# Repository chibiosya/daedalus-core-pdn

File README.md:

# daedalus-core-pdn

Supplied KiCad 8 board asset for the Daedalus core power-delivery-network (PDN) exercise: a
60 x 40 mm, 4-layer board carrying a 225-ball SoC (U1) with its core-supply fanout, a VRM output
(U2), a GND plane, a VDD_CORE plane, four mounting holes and a set of named keepout areas. It is
meant to be designed *onto*: you add decoupling capacitors, their vias and tracks; everything that
is already here is a **supplied item** and must not be moved or changed.

| File | Purpose |
|---|---|
| `daedalus_core_pdn.kicad_pcb` | The board (KiCad 8 format, version 20240108, all footprints embedded, zones filled) |
| `daedalus_core_pdn.kicad_pro` | Project: numeric design-rule constraints and the `Default` net class |
| `daedalus_core_pdn.kicad_dru` | Custom rules: no via-in-pad, the keepout rules, the mounting-hole copper keepout |
| `supplied_items.json` | UUID + geometry of every supplied item (footprints, tracks, vias, zones, rule areas, edge cuts, groups) and the U1 ball map |
| `tools/` | Reproducible generator / zone filler / verifier / build script |
| `images/` | SVG renders of F.Cu, B.Cu, In1.Cu and In2.Cu |

**Keep the three `daedalus_core_pdn.*` files together.** `kicad-cli pcb drc` loads the `.kicad_pro`
and `.kicad_dru` that sit next to the board; without them KiCad falls back to its defaults
(0.2 mm net-class clearance) and the supplied BGA fanout no longer passes DRC.

## Validation status (KiCad 8.0.9, `kicad-cli`)

```
kicad-cli pcb drc --severity-error   --exit-code-violations daedalus_core_pdn.kicad_pcb   -> exit 0, 0 violations, 0 unconnected
kicad-cli pcb drc --severity-warning --exit-code-violations daedalus_core_pdn.kicad_pcb   -> exit 0, 0 violations (no warnings remain)
```

The keepout rules were proven to fire with a negative-test board (`tools/generate_board.py
--negative-test`): a C_0402 capacitor placed inside KO_BGA_TOP, a via inside KO_VRM, a track inside
KO_DDR_CHANNEL on B.Cu, a via inside KO_MH1 and a via inside a non-U2 SMD pad are each reported as
an error by the corresponding rule (`ko_bga_top`, `ko_vrm`, `ko_ddr_channel`, `ko_mh1` +
`mounting_hole_copper_keepout`, `no_via_in_pad`), and a via centred between two adjacent U1 balls
(A1/A2, at 94.8, 74.4) fails on `clearance` to the ball pads while `ko_bga_top` fires only on the
capacitor, not on any via. A positive-test board (`--positive-test`) with one via at an outer-ring
interstitial position of the ball grid (A1 + (0.4, 0.4) = 94.8, 74.8, inside KO_BGA_TOP but
outside the core 7x7 field) passes DRC with 0 violations. `tools/build.sh` re-runs both tests
every build.

## Board

* Outline: rectangle 60 x 40 mm on Edge.Cuts, corners (70,60) (130,60) (130,100) (70,100). All
  coordinates in this document are KiCad board coordinates in mm (x to the right, y downwards).
* Finished thickness 1.54 mm, 4 copper layers. Stackup is stored in the board file
  (Board Setup > Physical Stackup):

| # | Layer | Type | Thickness | Note |
|---|---|---|---|---|
| 1 | F.Cu | copper | 0.035 mm | signal, components |
| | dielectric 1 | prepreg FR4 | 0.200 mm | |
| 2 | In1.Cu | copper | 0.035 mm | GND plane |
| | dielectric 2 | core FR4 | 1.000 mm | |
| 3 | In2.Cu | copper | 0.035 mm | VDD_CORE plane |
| | dielectric 3 | prepreg FR4 | 0.200 mm | |
| 4 | B.Cu | copper | 0.035 mm | signal |

Solder-mask layers are entered with 0 thickness so the stackup total shown by KiCad equals the
specified 1.54 mm.

* Nets: `GND` (net 1) and `VDD_CORE` (net 2). There are no other nets; 176 of the U1 balls are
  intentionally unconnected.
* Planes: In1.Cu is a filled GND zone, In2.Cu a filled VDD_CORE zone. Both cover the board with a
  1.0 mm clearance to the edge (outline (71,61)-(129,99)), zone clearance 0.1 mm, minimum width
  0.2 mm, solid (no thermal relief) connections. The fills are stored in the file.
* Mounting holes H1..H4: non-plated 3.2 mm drill at (73,63), (127,63), (73,97), (127,97). Copper is
  kept 3.5 mm (radius) away from each hole centre on every layer, see `mounting_hole_copper_keepout`
  below and the KO_MH rule areas.

## U1: SoC BGA (supplied, do not change)

* Footprint `BGA-225_15x15_0.8mm`, reference U1, centre (100.000, 80.000), rotation 0, body
  12 x 12 mm, courtyard (F.CrtYd) 13 x 13 mm centred on U1.
* 15 x 15 balls on a 0.8 mm pitch. Pad: SMD circle 0.400 mm, NSMD (solder-mask margin +0.05 mm).
  Rows A B C D E F G H J K L M N P R (JEDEC, I/O/Q skipped), columns 1..15. Ball A1 is top-left in
  the KiCad view at (94.4, 74.4); ball R15 is bottom-right at (105.6, 85.6). Ball (row r, col c)
  is at x = 94.4 + 0.8 (c-1), y = 74.4 + 0.8 (index of r).
* Core region: the central 7 x 7 balls, rows E..L (E F G H J K L) x columns 5..11, checkerboard:
  `VDD_CORE` where (i + j) is even (25 balls), `GND` where odd (24 balls), i,j = 0..6 inside the
  block. Every other ball has no net.

Ball map (V = VDD_CORE, G = GND, . = no net):

| row \ col | 1 | 2 | 3 | 4 | 5 | 6 | 7 | 8 | 9 | 10 | 11 | 12 | 13 | 14 | 15 |
|---|---|---|---|---|---|---|---|---|---|---|---|---|---|---|---|
| **A** | . | . | . | . | . | . | . | . | . | . | . | . | . | . | . |
| **B** | . | . | . | . | . | . | . | . | . | . | . | . | . | . | . |
| **C** | . | . | . | . | . | . | . | . | . | . | . | . | . | . | . |
| **D** | . | . | . | . | . | . | . | . | . | . | . | . | . | . | . |
| **E** | . | . | . | . | V | G | V | G | V | G | V | . | . | . | . |
| **F** | . | . | . | . | G | V | G | V | G | V | G | . | . | . | . |
| **G** | . | . | . | . | V | G | V | G | V | G | V | . | . | . | . |
| **H** | . | . | . | . | G | V | G | V | G | V | G | . | . | . | . |
| **J** | . | . | . | . | V | G | V | G | V | G | V | . | . | . | . |
| **K** | . | . | . | . | G | V | G | V | G | V | G | . | . | . | . |
| **L** | . | . | . | . | V | G | V | G | V | G | V | . | . | . | . |
| **M** | . | . | . | . | . | . | . | . | . | . | . | . | . | . | . |
| **N** | . | . | . | . | . | . | . | . | . | . | . | . | . | . | . |
| **P** | . | . | . | . | . | . | . | . | . | . | . | . | . | . | . |
| **R** | . | . | . | . | . | . | . | . | . | . | . | . | . | . | . |

* Dog-bone fanout, one per core ball (49): F.Cu track, width 0.15 mm, from the ball centre to a via
  at (+0.400, +0.400) mm from the ball centre (towards +x, +y, i.e. down-right in the view).
  Via: through-hole, drill 0.200 mm, diameter 0.450 mm, same net as the ball. The vias sit on the
  interstitial positions of the ball grid, at x = 94.8 + 0.8 (c-1), y = 74.8 + 0.8 (row index),
  for c = 5..11 and row index 4..10. All 49 tracks and 49 vias are members of the group
  `U1_FANOUT`.

## U2: VRM output (supplied, do not change)

* Footprint `VRM_OUT`, reference U2, centre (75.000, 80.000), courtyard 6 x 8 mm centred on U2.
* Pad 1, net `VDD_CORE`: SMD rectangle 4.0 x 3.0 mm on F.Cu centred at (75.0, 78.0).
* Pad 2, net `GND`: SMD rectangle 4.0 x 3.0 mm on F.Cu centred at (75.0, 82.0).
* 4 through vias per pad, drill 0.3 mm, diameter 0.6 mm, same net as the pad, at
  x = 73.8 and 76.2, y = pad centre y -0.8 and +0.8, i.e. (73.8|76.2, 77.2|78.8) for pad 1 and
  (73.8|76.2, 81.2|82.8) for pad 2. These 8 vias are members of the group `U2_VIAS`.

## Via sizes

| Use | Diameter | Drill | Annular ring |
|---|---|---|---|
| U1 dog-bone vias (49) | 0.450 mm | 0.200 mm | 0.125 mm |
| U2 output vias (8) | 0.600 mm | 0.300 mm | 0.150 mm |
| `Default` net class via (for anything you add) | 0.450 mm | 0.200 mm | 0.125 mm |

## Keepouts (rule areas)

The keepouts are **named rule areas with no keepout flags of their own**; the enforcement lives in
`daedalus_core_pdn.kicad_dru` so that supplied items can be exempted while anything added later
is checked. Inside each area footprints, vias and tracks are forbidden on the listed layers, with
one exception: KO_BGA_TOP forbids footprints and tracks only. **Vias are allowed under the BGA**,
subject to the normal rules against the ball pads (0.100 mm clearance, 0.250 mm hole-to-copper
clearance, `no_via_in_pad`). In practice that means the interstitial positions of the ball grid
(ball centre + (±0.4, ±0.4) mm), where the supplied dog-bone vias already sit with 0.141 mm
clearance; a via centred between two adjacent balls overlaps their pads and fails.

| Name | Layers | Forbids | Shape | Coordinates (mm) | Exempt supplied items |
|---|---|---|---|---|---|
| KO_BGA_TOP | F.Cu | footprints, tracks (vias allowed) | 14 x 14 mm square | x 93..107, y 73..87 (centre 100,80) | U1, group U1_FANOUT |
| KO_DDR_CHANNEL | F.Cu, B.Cu | footprints, vias, tracks | rectangle | x 108..130, y 64..96 | none |
| KO_CONNECTOR | F.Cu, B.Cu | footprints, vias, tracks | rectangle | x 70..90, y 60..70 | H1 |
| KO_VRM | F.Cu, B.Cu | footprints, vias, tracks | rectangle | x 70..81, y 74..86 | U2, group U2_VIAS |
| KO_MH1 | all copper | footprints, vias, tracks | circle r 3.5 mm (72-gon) | centre (73,63) | H1 |
| KO_MH2 | all copper | footprints, vias, tracks | circle r 3.5 mm (72-gon) | centre (127,63) | H2 |
| KO_MH3 | all copper | footprints, vias, tracks | circle r 3.5 mm (72-gon) | centre (73,97) | H3 |
| KO_MH4 | all copper | footprints, vias, tracks | circle r 3.5 mm (72-gon) | centre (127,97) | H4 |

Rule areas in KiCad are polygons, so each circle is a 72-sided polygon with its vertices on the
3.5 mm radius. A footprint counts as inside an area when its courtyard intersects the area
(KiCad semantics), so give your capacitors a courtyard.

## Design rules

Numeric constraints (`.kicad_pro`, Board Setup > Constraints):

| Constraint | Value |
|---|---|
| Minimum clearance | 0.100 mm |
| Minimum track width | 0.150 mm |
| Minimum via diameter | 0.450 mm |
| Minimum via drill (through hole) | 0.200 mm |
| Minimum annular ring | 0.125 mm |
| Hole-to-hole clearance | 0.250 mm |
| Copper-to-hole clearance | 0.250 mm (KiCad default) |
| Copper-to-edge clearance | 0.500 mm |
| Courtyard overlap | error |
| Silkscreen / solder-mask rules | KiCad defaults |

Net class `Default`: clearance 0.100 mm, track width 0.200 mm, via 0.450 / 0.200 mm. (The clearance
is set equal to the minimum clearance because KiCad's default of 0.2 mm would fail the specified
BGA fanout, whose via-to-neighbouring-ball gap is 0.141 mm.)

Custom rules (`.kicad_dru`, KiCad 8 syntax):

```
(rule no_via_in_pad
	(condition "A.Type == 'Via' && B.Type == 'Pad' && B.Pad_Type == 'SMD' && !B.memberOfFootprint('U2')")
	(constraint physical_clearance (min 0.1mm)))
```
No via may touch or come within 0.1 mm of any SMD pad, regardless of net. U2's pads are supplied
with vias inside them and are the only exemption.

```
(rule ko_bga_top
	(layer "F.Cu")
	(condition "A.intersectsArea('KO_BGA_TOP') && !A.memberOfFootprint('U1') && !(A.Type == 'Footprint' && A.Reference == 'U1') && !A.memberOfGroup('U1_FANOUT')")
	(constraint disallow footprint track))
```
One such rule per keepout (`ko_bga_top`, `ko_ddr_channel`, `ko_connector`, `ko_vrm`, `ko_mh1..4`),
each restricted to the area's layers (`(layer outer)` for F.Cu + B.Cu, no layer clause for
all-copper) and exempting only the supplied items listed in the table above. All of them except
`ko_bga_top` use `(constraint disallow footprint via track)`; `ko_bga_top` omits `via`, so vias
under the BGA are governed by the clearance, hole-to-copper and `no_via_in_pad` rules only.

```
(rule mounting_hole_copper_keepout
	(condition "B.Pad_Type == 'NPTH, mechanical'")
	(constraint hole_clearance (min 1.9mm)))
```
Hole edge (radius 1.6 mm) + 1.9 mm = the 3.5 mm copper-free radius around each mounting hole. This
is honoured by the zone filler (the planes already have the cut-outs) and by DRC for any copper
you add.

Capacitor via proximity is checked by the grader, not by DRC.

## Capacitor footprints you may use

From the official KiCad library `Capacitor_SMD`: `C_0201_0603Metric`, `C_0402_1005Metric`,
`C_0603_1608Metric`, `C_0805_2012Metric`, `C_1210_3225Metric`. The `Value` field must be exactly
one of `0.1uF 0.22uF 0.47uF 1.0uF 2.2uF 4.7uF 10uF 22uF 47uF 100uF` (as allowed per package in the
brief).

## Supplied items

`supplied_items.json` lists every supplied object with its UUID and geometry: 6 footprints (U1, U2,
H1..H4), 49 tracks, 57 vias, 2 planes, 8 rule areas, the Edge.Cuts rectangle and the 2 groups, plus
the U1 ball map. UUIDs are deterministic (UUID v5 of the item name) so a regenerated board has the
same IDs. `python3 tools/verify_board.py daedalus_core_pdn.kicad_pcb supplied_items.json` checks
that all of them are still present and that the geometry matches this document.

## Rebuilding

```
KICAD_APP=/Applications/KiCad/KiCad.app tools/build.sh
```
`tools/generate_board.py` (stdlib Python, no KiCad needed) writes the three KiCad files and
`supplied_items.json` from the numbers above; `tools/finalize_board.py` (KiCad's bundled python,
`pcbnew`) fills the zones and re-saves in canonical KiCad 8 format; `tools/build.sh` then runs
DRC at error and warning severity, the negative and positive keepout tests, the verifier and the
SVG exports.
Built and validated with KiCad 8.0.9 on macOS.

## Renders

| F.Cu | B.Cu |
|---|---|
|  |  |

| In1.Cu (GND plane) | In2.Cu (VDD_CORE plane) |
|---|---|
|  |  |

## Notes and assumptions

* The mounting-hole footprints have no courtyard on purpose: KiCad tests "footprint in area" with
  the courtyard, and the holes sit inside their own KO_MH areas and (H1) inside KO_CONNECTOR.
* Solder-mask thickness is 0 in the stackup so the total equals 1.54 mm; nothing else depends on it.
* Keepout rules use `intersectsArea` (any overlap is a violation), the same test KiCad uses for its
  own rule-area keepouts.
* Reference designators of H1..H4 are hidden; U1/U2 references are on F.SilkS outside their pads.

## Changelog

* **v1.1 (2026-10-24)**: `ko_bga_top` no longer disallows vias (`disallow footprint track`
  instead of `disallow footprint via track`). The keepout was meant to keep components and tracks
  off the top side under the BGA, not to forbid through vias at the interstitial positions of the
  ball grid, which the supplied dog-bones already use. Vias under the BGA are governed by the
  normal clearance, hole-to-copper and `no_via_in_pad` rules. Negative test extended (via between
  two balls must fail on clearance) and a positive test added (interstitial via must pass). Board,
  project file and `supplied_items.json` are unchanged.
* **v1.0 (2026-10-23)**: initial release.

## Licence

CC0 1.0 Universal (public domain dedication), see `LICENSE`.

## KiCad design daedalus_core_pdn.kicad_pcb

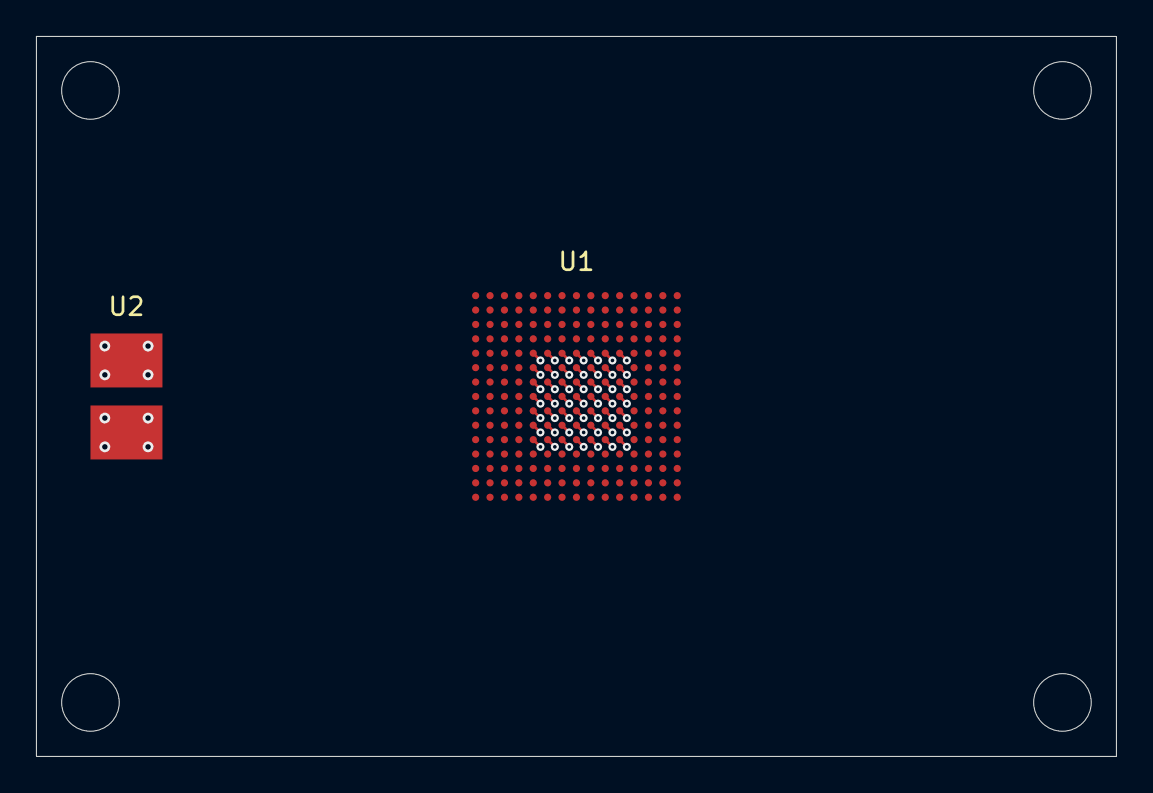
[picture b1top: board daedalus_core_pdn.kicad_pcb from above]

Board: 4 copper layers, 60.0 x 40.0 mm, 6 parts (0 on the bottom side), 2 nets.

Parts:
H1, H2, H3, H4: MountingHole_3.2mm
U1: SoC; BGA-225_15x15_0.8mm
U2: VRM_OUT

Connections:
GND: U1.E6, U1.E8, U1.E10, U1.F5, U1.F7, U1.F9, U1.F11, U1.G6, U1.G8, U1.G10, U1.H5, U1.H7, U1.H9, U1.H11, U1.J6, U1.J8, U1.J10, U1.K5, U1.K7, U1.K9, U1.K11, U1.L6, U1.L8, U1.L10, U2.2
VDD_CORE: U1.E5, U1.E7, U1.E9, U1.E11, U1.F6, U1.F8, U1.F10, U1.G5, U1.G7, U1.G9, U1.G11, U1.H6, U1.H8, U1.H10, U1.J5, U1.J7, U1.J9, U1.J11, U1.K6, U1.K8, U1.K10, U1.L5, U1.L7, U1.L9, U1.L11, U2.1
